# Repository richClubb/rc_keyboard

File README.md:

RC Keyboard
-----------

# Personalised design having fun with the idea of reducing keys down to a comfortable minimum.

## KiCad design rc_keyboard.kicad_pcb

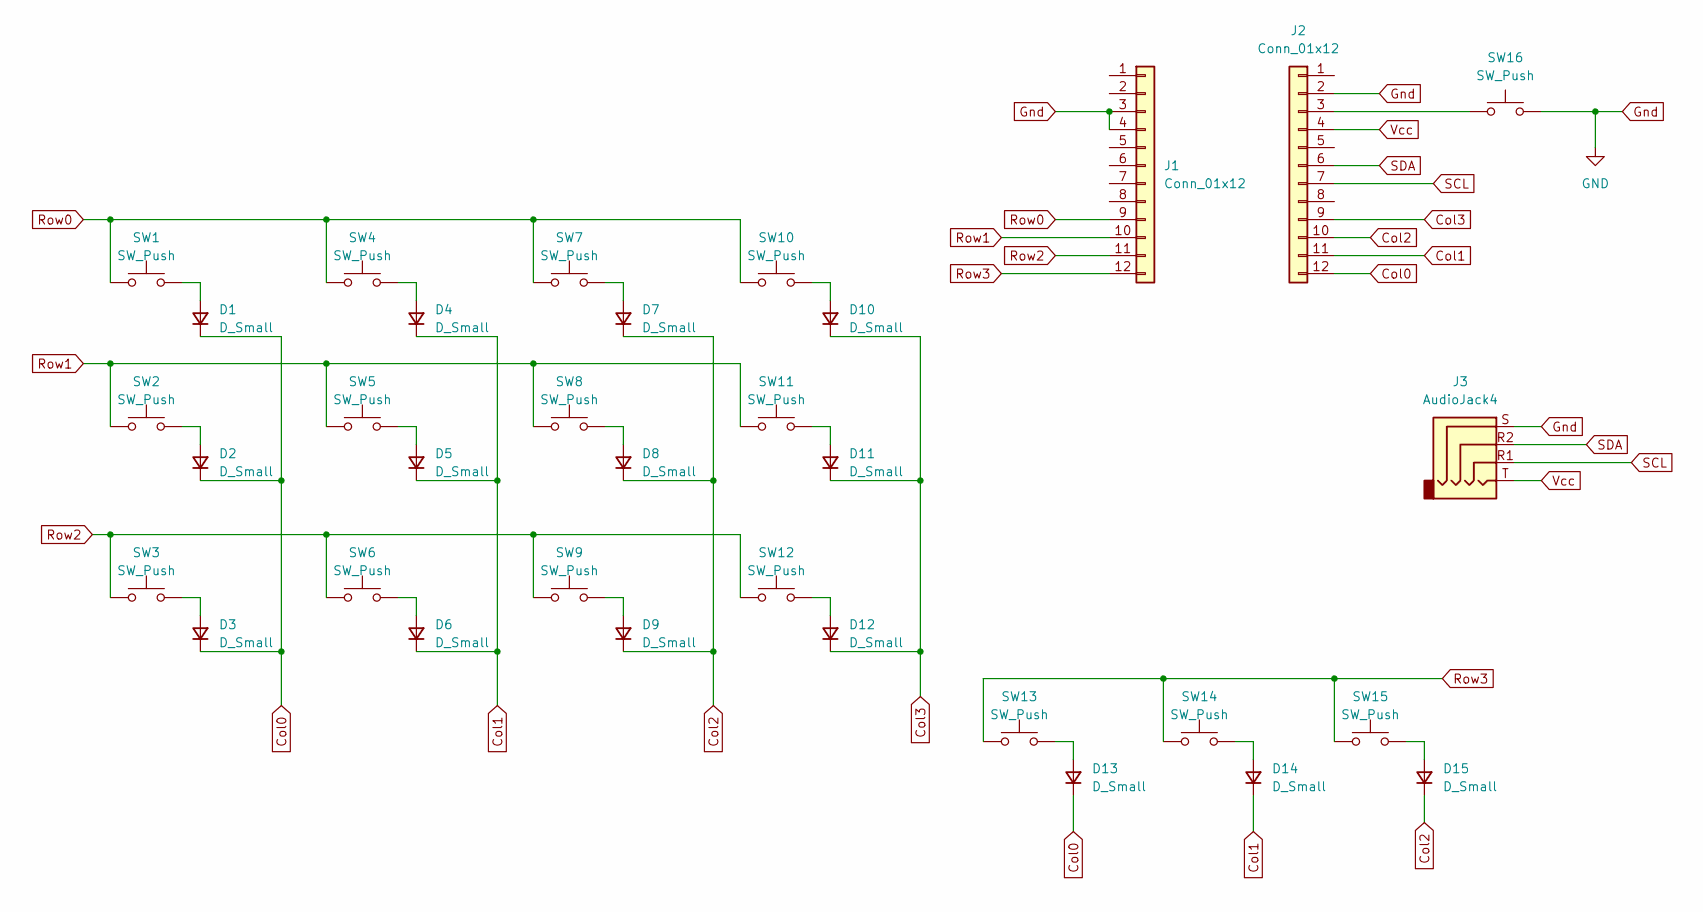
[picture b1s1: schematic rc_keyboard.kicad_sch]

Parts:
D1, D2, D3, D4, D5, D6, D7, D8, D9, D10, D11, D12, D13, D14, D15: D_Small; D_0603_1608Metric
J1, J2: Conn_01x12; PinSocket_1x12_P2.54mm_Vertical
J3: AudioJack4; Jack_3.5mm_PJ320E_Horizontal
SW1, SW2, SW3, SW4, SW5, SW6, SW7, SW8, SW9, SW10, SW11, SW12, SW13, SW14, SW15: SW_Push; SW_Cherry_MX_1.00u_PCB
SW16: SW_Push; SW_PUSH_6mm_H4.3mm

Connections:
Col0: D1.1 (K), D2.1 (K), D3.1 (K), D13.1 (K), J2.12
Col1: D4.1 (K), D5.1 (K), D6.1 (K), D14.1 (K), J2.11
Col2: D7.1 (K), D8.1 (K), D9.1 (K), D15.1 (K), J2.10
Col3: D10.1 (K), D11.1 (K), D12.1 (K), J2.9
Gnd: J1.3, J1.4, J2.2, J3.S, SW16.2
unnamed: D1.2 (A), SW1.2
unnamed: D2.2 (A), SW2.2
unnamed: D3.2 (A), SW3.2
unnamed: D4.2 (A), SW4.2
unnamed: D5.2 (A), SW5.2
unnamed: D6.2 (A), SW6.2
unnamed: D7.2 (A), SW7.2
unnamed: D8.2 (A), SW8.2
unnamed: D9.2 (A), SW9.2
unnamed: D10.2 (A), SW10.2
unnamed: D11.2 (A), SW11.2
unnamed: D12.2 (A), SW12.2
unnamed: D13.2 (A), SW13.2
unnamed: D14.2 (A), SW14.2
unnamed: D15.2 (A), SW15.2
unnamed: J2.3, SW16.1
Row0: J1.9, SW1.1, SW4.1, SW7.1, SW10.1
Row1: J1.10, SW2.1, SW5.1, SW8.1, SW11.1
Row2: J1.11, SW3.1, SW6.1, SW9.1, SW12.1
Row3: J1.12, SW13.1, SW14.1, SW15.1
SCL: J2.7, J3.R1
SDA: J2.6, J3.R2
Vcc: J2.4, J3.T

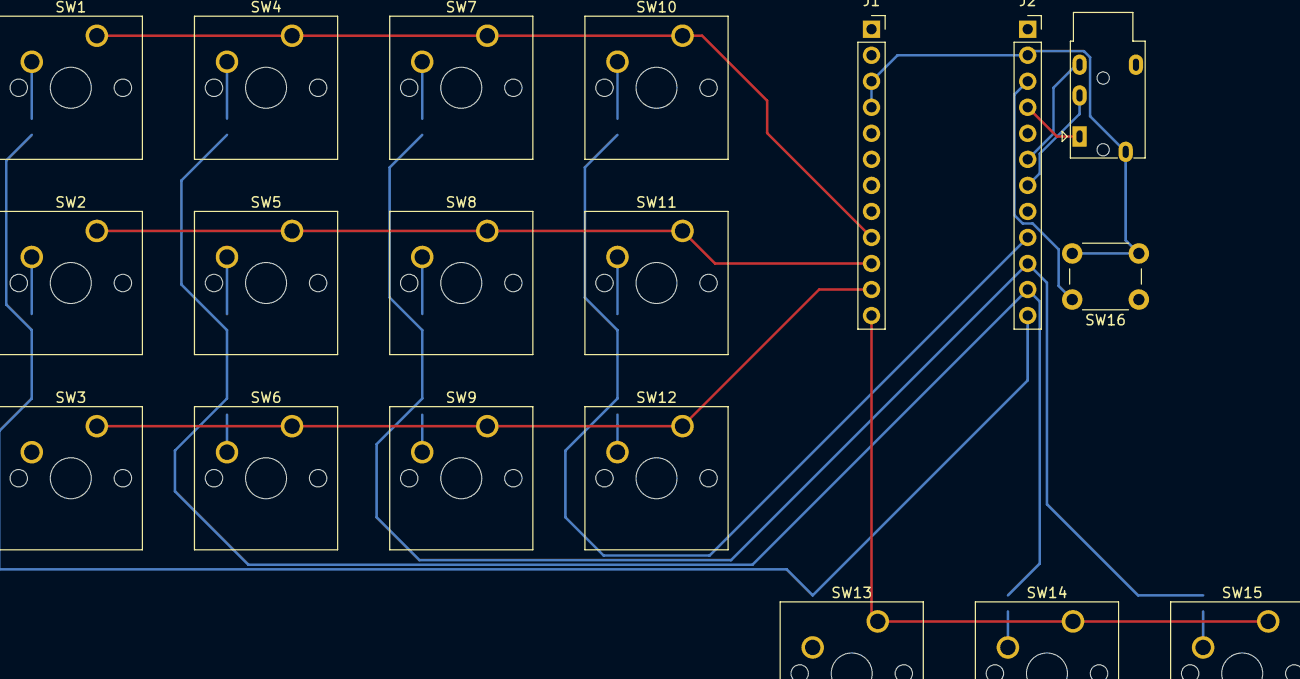
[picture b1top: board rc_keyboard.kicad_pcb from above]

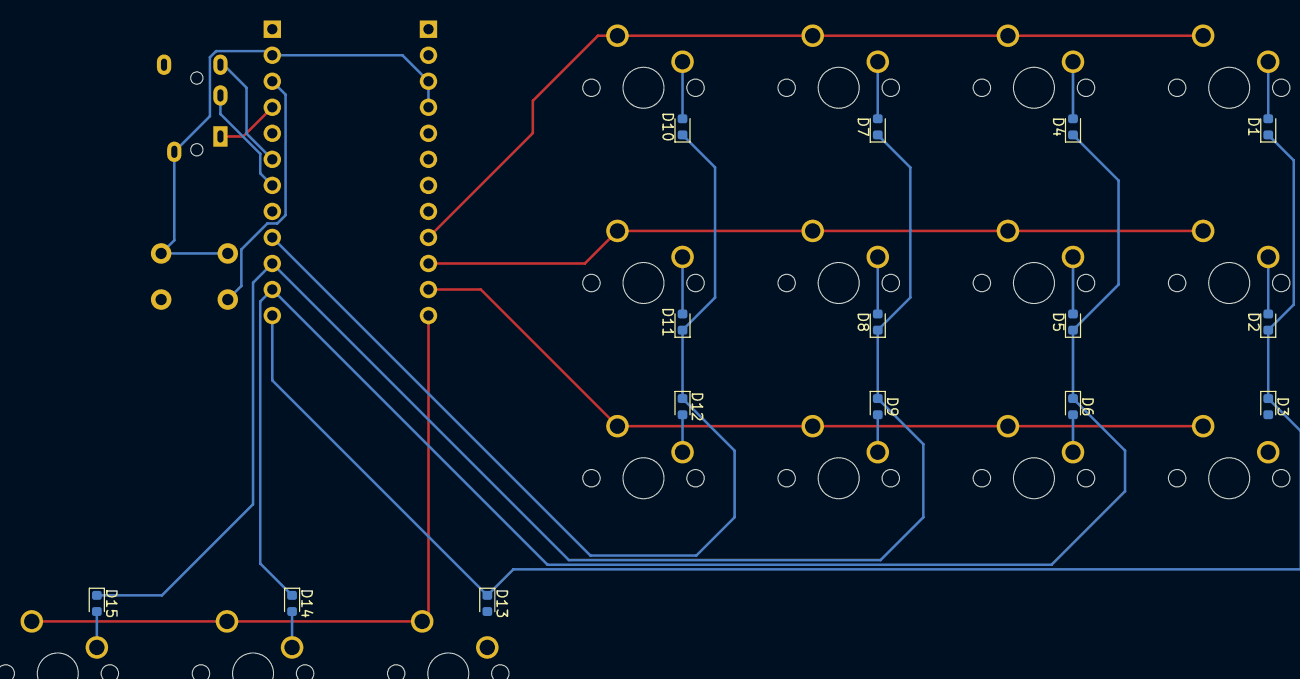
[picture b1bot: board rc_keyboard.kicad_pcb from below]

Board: 2 copper layers, 34 parts (15 on the bottom side), 28 nets.
